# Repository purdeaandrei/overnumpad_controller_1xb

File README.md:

# OverNumpad Controller

This is a replacement keyboard controller, for 4th generation IBM/Lexmark
Model M keyboards, and Unicomp keyboards that use the same mounting style
over the numpad.

Licensed under CERN-OHL-P v2 or later

## Images

## Keyboards supported

Only some of the listed supported keyboards has been tested at the time of release.
Some keyboards may require additional software work for support.
This list may change in the future.

* IBM/Lexmark 4th generation Model M keyboards
  See [here](https://deskthority.net/wiki/IBM_Enhanced_Keyboard) for more detail on IBM Model M keyboard generations.
  The easiest way to identify IBM/Lexmark keyboards supported by this controller is to look at the lock lights led alignment.
  Top-aligned leds means that the controller is located over the numpad, and may be replaced by this controller.
  However this controller also provides a solder jumper option, for a set of leds that are compatible with bottom-aligned
  locklight stickers.

* Various Unicomp keyboards, that use the same mounting mechanism, including:
  * Spacesaver M keyboards
  * Ultra Classic keyboards
  * Classic keyboards
  * New Model M keyboards
  * PC122 keyboards
  * The following exceptions apply:
    * The Mini M uses a bottom-mounted controller, therefore it's not supported
    * This controller may be used on keyboards that include additional input devices, such as trackballs, and pointing sticks,
      and card readers, but the controller will not support the additional devices.

## Two versions are available
The mounting holes on the controller can come in two variants:
### 3.2mm mounting holes version
* Used by IBM/Lexmark 4th generation Model M keyboards
* Used by some Unicomp keyboards, generally the older, the more likely that it uses a small-hole controller
* The small-hole variant will not fit on keyboards that use big-hole controllers
### 4.3mm mounting holes version
* Used by some Unicomp keyboards, generally the newer, the more likely that it uses a big-hole controller
* The big-hole controller will not be securely held in place, and will likely not work correctly if it is mounted on a keyboard with a small-hole controller.

## How to order from JLCPCB:
1. Go to http://jlcpcb.com , sign in to your account (create one if you don't have one)
2. Click Order Now
3. Upload the .zip file from the "order" subfolder. Make sure to select the correct version.
4. Select PCB Qty you wish to build
5. Set "Remove Order Number" to "Specify a location"
6. Scroll down, turn on the "SMT Assembly" option
7. Select "Assemble top side"
8. Select "Tooling holes" = "Added by Customer"
9. Click "I agree to the Terms and Conditions..."
10. Click "Next" on the right side
11. Click "Add BOM File", upload the "*_bom_jlc.csv" file from the "order" subfolder.
12. Click "Add CPL File", upload the "*_cpl_jlc.csv" file from the "order" subfolder.
13. Click "Next"
14. Make sure that all parts say "Confirmed" with a little check box in the final column. If it shows a greyed out "confirm", or a yellow "Inventory shortage", or there is a red "No parts selected" in the Matched Part Detail column, then some parts may be out of stock. (If parts are out of stock then your options are Wait until it's back in stock / Find equivalent replacement with correct footprint, if it is in the JLCPCB parts library / Redesign the board with a different component / Order the missing part from another supplier and solder it yourself )
15. Click "Next"
16. Double-check components look correctly rotated (this is expected to be correct unless JLCPCB makes changes to their system)
17. Double-check again, that Selected Parts has the correct number of items (21 items for v1.1b), and that Unselected Parts has 0 items.
18. Save to Cart, Check Out.

## Components of this design that have to be ordered separately:
The connectors for the USB cable, and for the solenoid driver need to be ordered separately. Compatible connectors are available from a variety of manufacturers, and distributors, one example:
* Through-hole male connector: https://www.tme.eu/en/details/ds1066-4mrw6sa/raster-signal-connectors-2-00mm/connfly/
* Female connector (for USB cable, or for ribbon cable): https://www.tme.eu/en/details/i-ds1066-scw04/raster-signal-connectors-2-00mm/connfly/
* Crimp pins for the female connector: https://www.tme.eu/en/details/t-ds1066-sc600/raster-signal-connectors-2-00mm/connfly/

## Firmware

Currently QMK firmware, and VIAL-QMK firmware are available.

For VIAL-QMK please see here:
https://github.com/purdeaandrei/vial-qmk-overnumpad-and-aristides-2862/releases/latest

For plain QMK please look for keyboards called `unicomp/*/overnumpad_1xb`, and `ibm/*/overnumpad_1xb` in upstream QMK.

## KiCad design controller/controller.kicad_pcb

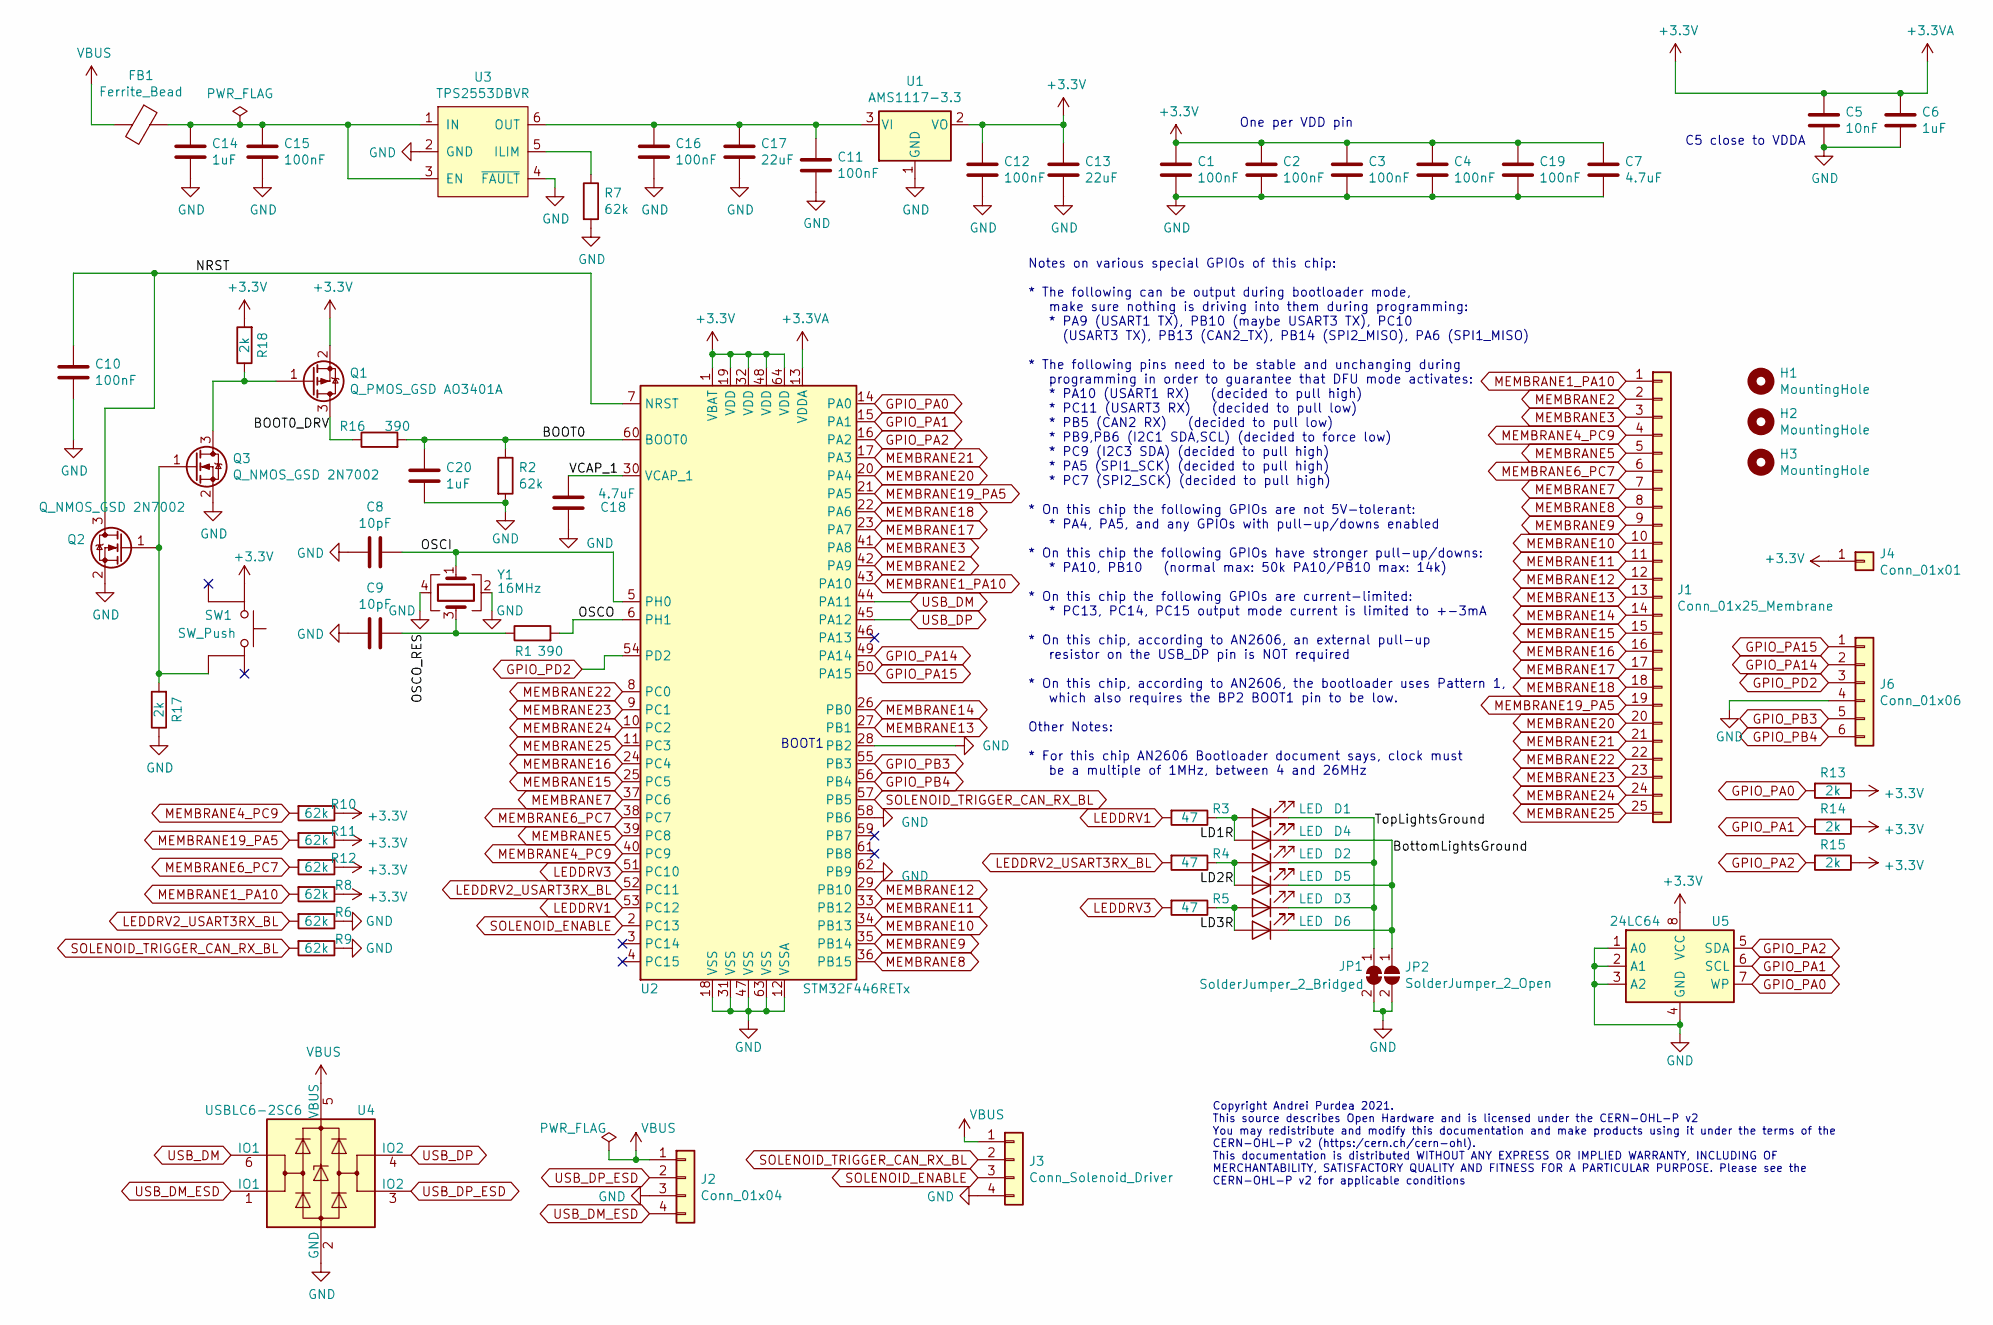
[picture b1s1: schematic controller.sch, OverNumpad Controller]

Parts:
C1, C2, C3, C4, C10, C11, C12, C15, C16, C19: 100nF; C_0805_2012Metric_Pad1.15x1.40mm_HandSolder; LCSC C49678
C5: 10nF; C_0805_2012Metric_Pad1.15x1.40mm_HandSolder; LCSC C1710
C6, C14, C20: 1uF; C_0805_2012Metric_Pad1.15x1.40mm_HandSolder; LCSC C28323
C7, C18: 4.7uF; C_0805_2012Metric_Pad1.15x1.40mm_HandSolder; LCSC C1779
C8, C9: 10pF; C_0805_2012Metric_Pad1.15x1.40mm_HandSolder; LCSC C1785
C13, C17: 22uF; C_0805_2012Metric_Pad1.15x1.40mm_HandSolder; LCSC C45783
D1, D2, D3, D4, D5, D6: LED; LED_0805_2012Metric_Pad1.15x1.40mm_HandSolder; LCSC C2296
FB1: Ferrite_Bead; L_0805_2012Metric_Pad1.15x1.40mm_HandSolder; LCSC C1015
H1, H2, H3: MountingHole; tooling_hole
J1: Conn_01x25_Membrane; membrane_connector
J2: Conn_01x04; JST_PH_S4B-PH-K_1x04_P2.00mm_Horizontal
J3: Conn_Solenoid_Driver; JST_PH_S4B-PH-K_1x04_P2.00mm_Horizontal
J4: Conn_01x01; PinHeader_1x01_P1.27mm_Vertical_mod_no_courtyard_no_ref
J6: Conn_01x06; PinHeader_1x06_P1.27mm_Vertical
JP1: SolderJumper_2_Bridged; shortable_shorted
JP2: SolderJumper_2_Open; shortable
Q1: Q_PMOS_GSD AO3401A; SOT-23; LCSC C15127
Q2, Q3: Q_NMOS_GSD 2N7002; SOT-23; LCSC C8545
R1, R16: 390; R_0805_2012Metric_Pad1.15x1.40mm_HandSolder; LCSC C17655
R2, R6, R7, R8, R9, R10, R11, R12: 62k; R_0805_2012Metric_Pad1.15x1.40mm_HandSolder; LCSC C17783
R3, R4, R5: 47; R_0805_2012Metric_Pad1.15x1.40mm_HandSolder; LCSC C17714
R13, R14, R15, R17, R18: 2k; R_0805_2012Metric_Pad1.15x1.40mm_HandSolder; LCSC C17604
SW1: SW_Push; switch_K2-1187SQ-A4SW-06; LCSC C92584
U1: AMS1117-3.3; SOT-223-3_TabPin2; LCSC C6186
U2: STM32F446RETx; LQFP-64_10x10mm_P0.5mm; LCSC C69336
U3: TPS2553DBVR; SOT-23-6_Handsoldering; LCSC C55266
U4: USBLC6-2SC6; SOT-666; LCSC C15999
U5: 24LC64; SOIC-8_3.9x4.9mm_P1.27mm; LCSC C79988
Y1: 16MHz; Crystal_SMD_3225-4Pin_3.2x2.5mm_HandSoldering; LCSC C13738

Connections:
+3.3VA: C1.1, C2.1, C3.1, C4.1, C5.1, C6.1, C7.1, C12.1, C13.1, C19.1, J4.1, Q1.2 (S), R8.1, R10.1, R11.1, R12.1, R13.1, R14.1, R15.1, R18.2, SW1.1, U1.2 (VO), U2.1 (VBAT), U2.13 (VDDA), U2.19 (VDD), U2.32 (VDD), U2.48 (VDD), U2.64 (VDD), U5.8 (VCC)
/BOOT0: C20.1, R2.1, R16.2, U2.60 (BOOT0)
/BOOT0_DRV: Q1.3 (D), R16.1
/BottomLightsGround: D4.1 (K), D5.1 (K), D6.1 (K), JP2.1 (A)
/LD1R: D1.2 (A), D4.2 (A), R3.1
/LD2R: D2.2 (A), D5.2 (A), R4.1
/LD3R: D3.2 (A), D6.2 (A), R5.1
/NRST: C10.2, Q2.3 (D), U2.7 (NRST)
/OSCI: C8.1, U2.5 (PH0), Y1.1
/OSCO: R1.2, U2.6 (PH1)
/OSCO_RES: C9.1, R1.1, Y1.3
/TopLightsGround: D1.1 (K), D2.1 (K), D3.1 (K), JP1.1 (A)
/VCAP_1: C18.1, U2.30 (VCAP_1)
GND: C1.2, C2.2, C3.2, C4.2, C5.2, C6.2, C7.2, C8.2, C9.2, C10.1, C11.2, C12.2, C13.2, C14.2, C15.2, C16.2, C17.2, C18.2, C19.2, C20.2, J2.3, J3.4, J6.4, JP1.2 (B), JP2.2 (B), Q2.2 (S), Q3.2 (S), R2.2, R6.1, R7.2, R9.1, R17.1, U1.1 (GND), U2.12 (VSSA), U2.18 (VSS), U2.28 (PB2), U2.31 (VSS), U2.47 (VSS), U2.58 (PB6), U2.62 (PB9), U2.63 (VSS), U3.2 (GND), U3.4 (~FAULT), U4.2 (GND), U5.1 (A0), U5.2 (A1), U5.3 (A2), U5.4 (GND), Y1.2, Y1.4
GPIO_PA0: R13.2, U2.14 (PA0), U5.7 (WP)
GPIO_PA1: R14.2, U2.15 (PA1), U5.6 (SCL)
GPIO_PA2: R15.2, U2.16 (PA2), U5.5 (SDA)
GPIO_PA14: J6.2, U2.49 (PA14)
GPIO_PA15: J6.1, U2.50 (PA15)
GPIO_PB3: J6.5, U2.55 (PB3)
GPIO_PB4: J6.6, U2.56 (PB4)
GPIO_PD2: J6.3, U2.54 (PD2)
LEDDRV1: R3.2, U2.53 (PC12)
LEDDRV2_USART3RX_BL: R4.2, R6.2, U2.52 (PC11)
LEDDRV3: R5.2, U2.51 (PC10)
MEMBRANE1_PA10: J1.1, R8.2, U2.43 (PA10)
MEMBRANE2: J1.2, U2.42 (PA9)
MEMBRANE3: J1.3, U2.41 (PA8)
MEMBRANE4_PC9: J1.4, R10.2, U2.40 (PC9)
MEMBRANE5: J1.5, U2.39 (PC8)
MEMBRANE6_PC7: J1.6, R12.2, U2.38 (PC7)
MEMBRANE7: J1.7, U2.37 (PC6)
MEMBRANE8: J1.8, U2.36 (PB15)
MEMBRANE9: J1.9, U2.35 (PB14)
MEMBRANE10: J1.10, U2.34 (PB13)
MEMBRANE11: J1.11, U2.33 (PB12)
MEMBRANE12: J1.12, U2.29 (PB10)
MEMBRANE13: J1.13, U2.27 (PB1)
MEMBRANE14: J1.14, U2.26 (PB0)
MEMBRANE15: J1.15, U2.25 (PC5)
MEMBRANE16: J1.16, U2.24 (PC4)
MEMBRANE17: J1.17, U2.23 (PA7)
MEMBRANE18: J1.18, U2.22 (PA6)
MEMBRANE19_PA5: J1.19, R11.2, U2.21 (PA5)
MEMBRANE20: J1.20, U2.20 (PA4)
MEMBRANE21: J1.21, U2.17 (PA3)
MEMBRANE22: J1.22, U2.8 (PC0)
MEMBRANE23: J1.23, U2.9 (PC1)
MEMBRANE24: J1.24, U2.10 (PC2)
MEMBRANE25: J1.25, U2.11 (PC3)
unnamed: C11.1, C16.1, C17.1, U1.3 (VI), U3.6 (OUT)
unnamed: C14.1, C15.1, FB1.1, U3.1 (IN), U3.3 (EN)
unnamed: Q1.1 (G), Q3.3 (D), R18.1
unnamed: Q2.1 (G), Q3.1 (G), R17.2, SW1.4
unnamed: R7.1, U3.5 (ILIM)
SOLENOID_ENABLE: J3.3, U2.2 (PC13)
SOLENOID_TRIGGER_CAN_RX_BL: J3.2, R9.2, U2.57 (PB5)
USB_DM: U2.44 (PA11), U4.6 (IO1)
USB_DM_ESD: J2.4, U4.1 (IO1)
USB_DP: U2.45 (PA12), U4.4 (IO2)
USB_DP_ESD: J2.2, U4.3 (IO2)
VBUS: FB1.2, J2.1, J3.1, U4.5 (VBUS)

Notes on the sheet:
One per VDD pin
C5 close to VDDA
Notes on various special GPIOs of this chip: * The following can be output during bootloader mode, make sure nothing is driving into them during programming: * PA9 (USART1 TX), PB10 (maybe USART3 TX), PC10 (USART3 TX), PB13 (CAN2_TX), PB14 (SPI2_MISO), PA6 (SPI1_MISO) * The following pins need to b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
BOOT1
Copyright Andrei Purdea 2021. This source describes Open Hardware and is licensed under the CERN-OHL-P v2 You may redistribute and modify this documentation and make products using it under the terms of the CERN-OHL-P v2 (https:/cern.ch/cern-ohl). This documentation is distributed WITHOUT ANY EXPRE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

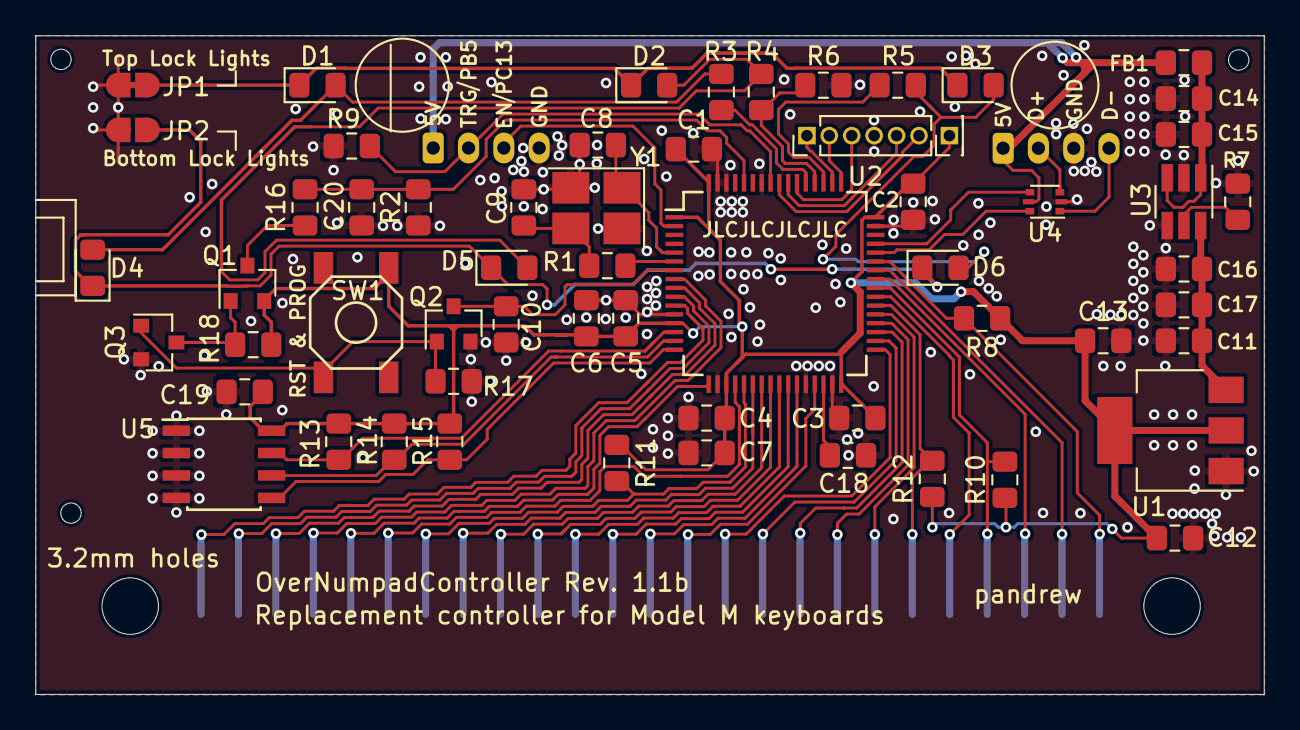
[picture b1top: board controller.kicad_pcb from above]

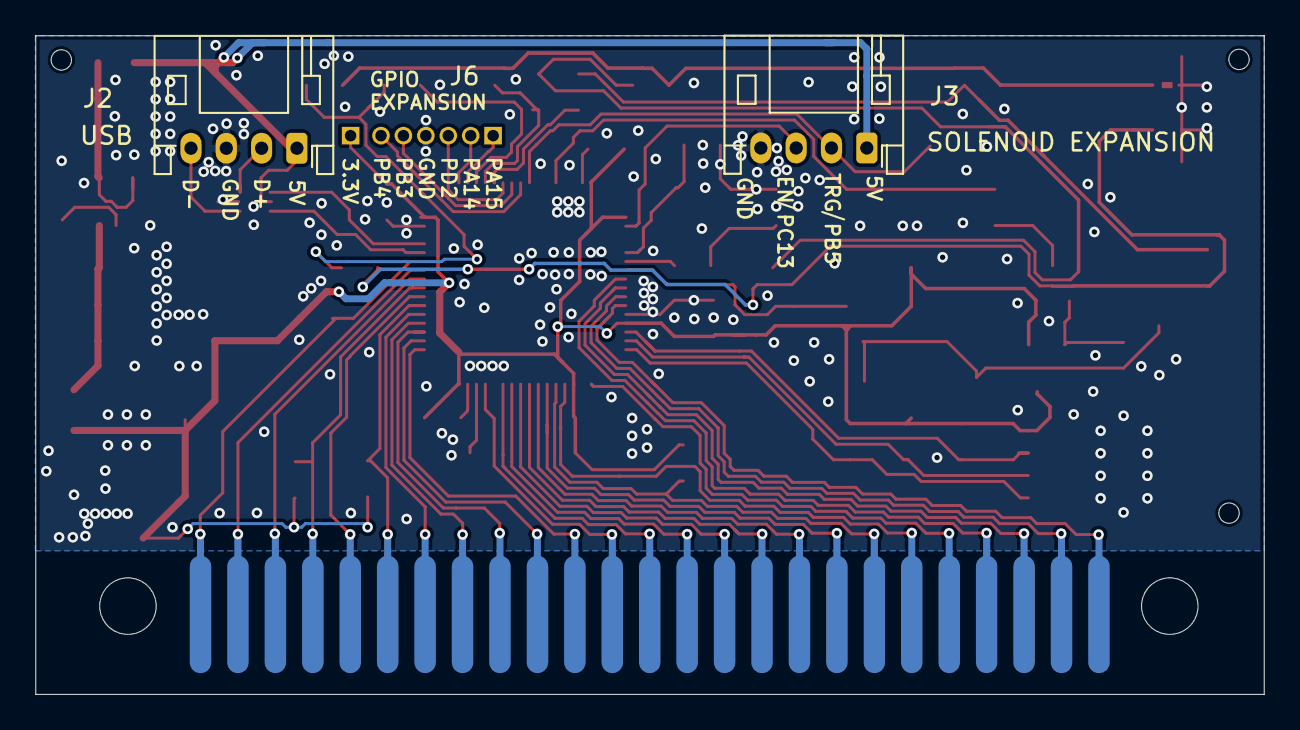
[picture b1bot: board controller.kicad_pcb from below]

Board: 2 copper layers, 69.6 x 37.3 mm, 65 parts (3 on the bottom side), 62 nets.

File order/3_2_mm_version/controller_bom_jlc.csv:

"Comment","Designator","Footprint","LCSC Part #"
"100nF","C1,C2,C3,C4,C10,C11,C12,C15,C16,C19","C_0805_2012Metric_Pad1.15x1.40mm_HandSolder","C49678"
"10nF","C5","C_0805_2012Metric_Pad1.15x1.40mm_HandSolder","C1710"
"1uF","C6,C14,C20","C_0805_2012Metric_Pad1.15x1.40mm_HandSolder","C28323"
"4.7uF","C7,C18","C_0805_2012Metric_Pad1.15x1.40mm_HandSolder","C1779"
"10pF","C8,C9","C_0805_2012Metric_Pad1.15x1.40mm_HandSolder","C1785"
"22uF","C13,C17","C_0805_2012Metric_Pad1.15x1.40mm_HandSolder","C45783"
"LED","D1,D2,D3,D4,D5,D6","LED_0805_2012Metric_Pad1.15x1.40mm_HandSolder","C2296"
"Ferrite_Bead","FB1","L_0805_2012Metric_Pad1.15x1.40mm_HandSolder","C1015"
"Q_PMOS_GSD AO3401A","Q1","SOT-23","C700954"
"Q_NMOS_GSD 2N7002","Q3,Q2","SOT-23","C8545"
"390","R1,R16","R_0805_2012Metric_Pad1.15x1.40mm_HandSolder","C17655"
"62k","R2,R7,R8,R6,R9,R11,R12,R10","R_0805_2012Metric_Pad1.15x1.40mm_HandSolder","C17783"
"47","R3,R4,R5","R_0805_2012Metric_Pad1.15x1.40mm_HandSolder","C17714"
"2k","R13,R14,R15,R18,R17","R_0805_2012Metric_Pad1.15x1.40mm_HandSolder","C17604"
"SW_Push","SW1","switch_K2-1187SQ-A4SW-06","C92584"
"AMS1117-3.3","U1","SOT-223-3_TabPin2","C6186"
"STM32F446RETx","U2","LQFP-64_10x10mm_P0.5mm","C69336"
"TPS2553DBVR","U3","SOT-23-6_Handsoldering","C55266"
"USBLC6-2SC6","U4","SOT-666","C15999"
"24LC64","U5","SOIC-8_3.9x4.9mm_P1.27mm","C79988"
"16MHz","Y1","Crystal_SMD_3225-4Pin_3.2x2.5mm_HandSoldering","C13738"

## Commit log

2020-12-08 added solenoid driver
2020-12-10 added gpio header and other updates
2020-12-10 LED current limit resistors changed to 47 ohm
2020-12-10 more updates
2021-01-24 Fixed switches -- they are SMD
2021-03-22 Overnumpad Controller v1.0
2021-03-22 Added version 1.0b, and exported 3mm version gerber
2021-03-22 Added 4.1mm hole variant gerbers
2021-04-10 manually fixed rotations
2021-04-25 Added v1.1b version
2021-04-25 Prepare the design for release
2021-04-25 Replacing LCSC reference for P-channel mosfet, to same transistor from different manufacturer.
2023-03-16 Replaced out-of-stock part
2023-03-16 fixed rotation of U2
